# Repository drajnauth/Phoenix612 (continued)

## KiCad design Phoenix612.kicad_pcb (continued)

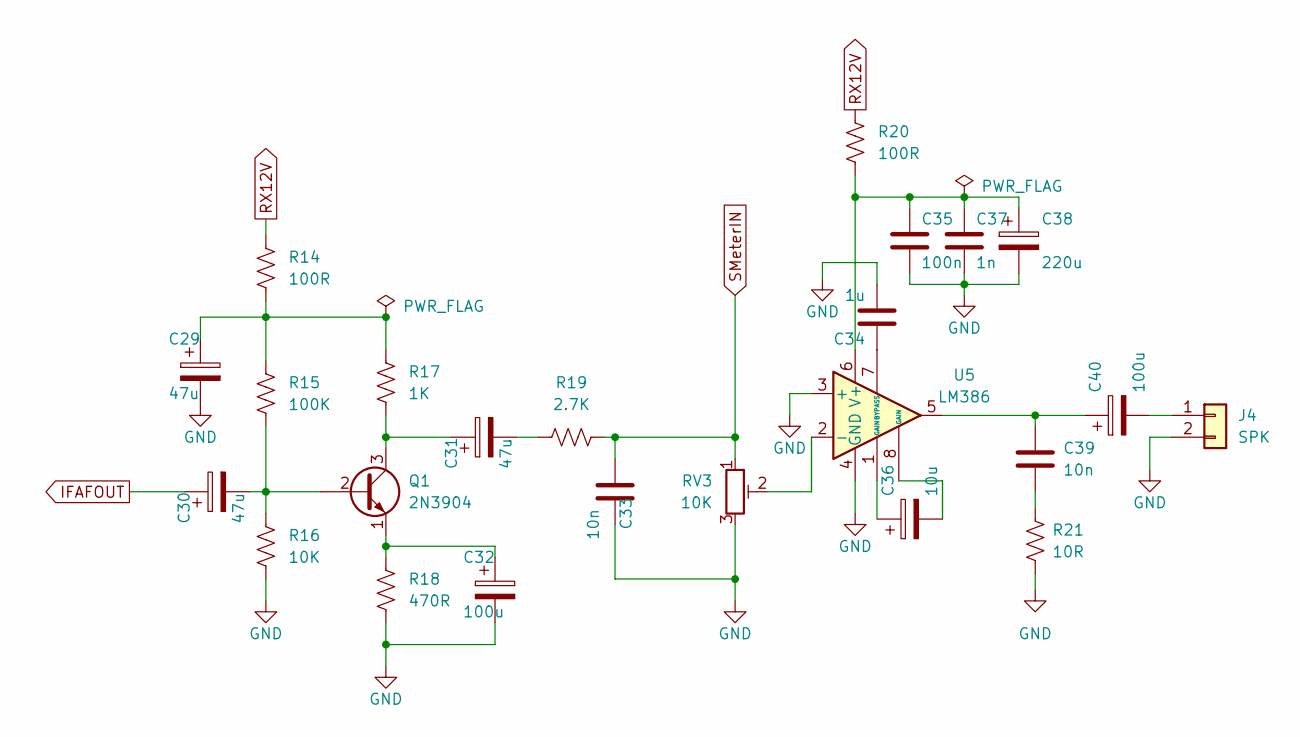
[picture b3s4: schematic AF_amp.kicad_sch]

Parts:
C29, C30, C31: 47u; CP_Radial_D8.0mm_P2.50mm
C32, C40: 100u; CP_Radial_D8.0mm_P2.50mm
C33, C39: 10n; C_Disc_D3.4mm_W2.1mm_P2.50mm
C34: 1u; C_Disc_D3.4mm_W2.1mm_P2.50mm
C35: 100n; C_Disc_D3.4mm_W2.1mm_P2.50mm
C36: 10u; CP_Radial_D8.0mm_P2.50mm
C37: 1n; C_Disc_D3.4mm_W2.1mm_P2.50mm
C38: 220u; CP_Radial_D8.0mm_P2.50mm
J4: SPK; PinHeader_1x02_P2.54mm_Vertical
Q1: 2N3904; TO-92_Inline
R14, R20: 100R; R_Axial_DIN0207_L6.3mm_D2.5mm_P10.16mm_Horizontal
R15: 100K; R_Axial_DIN0207_L6.3mm_D2.5mm_P10.16mm_Horizontal
R16: 10K; R_Axial_DIN0207_L6.3mm_D2.5mm_P10.16mm_Horizontal
R17: 1K; R_Axial_DIN0207_L6.3mm_D2.5mm_P10.16mm_Horizontal
R18: 470R; R_Axial_DIN0207_L6.3mm_D2.5mm_P10.16mm_Horizontal
R19: 2.7K; R_Axial_DIN0207_L6.3mm_D2.5mm_P10.16mm_Horizontal
R21: 10R; R_Axial_DIN0207_L6.3mm_D2.5mm_P10.16mm_Horizontal
RV3: 10K; Potentiometer_Bourns_3296W_Vertical
U5: LM386; DIP-8_W7.62mm_Socket

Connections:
GND: C29.2, C32.2, C33.2, C34.2, C35.2, C37.2, C38.2, J4.2, R16.2, R18.2, R21.1, RV3.3, U5.3 (+), U5.4 (GND); also elsewhere on the board
IFAFOUT: C30.1; also elsewhere on the board
unnamed: C29.1, R14.2, R15.1, R17.1
unnamed: C30.2, Q1.2 (B), R15.2, R16.1
unnamed: C31.1, Q1.3 (C), R17.2
unnamed: C31.2, R19.1
unnamed: C32.1, Q1.1 (E), R18.1
unnamed: C34.1, U5.7 (BYPASS)
unnamed: C35.1, C37.1, C38.1, R20.2, U5.6 (V+)
unnamed: C36.1, U5.1 (GAIN)
unnamed: C36.2, U5.8 (GAIN)
unnamed: C39.1, C40.1, U5.5
unnamed: C39.2, R21.2
unnamed: C40.2, J4.1
unnamed: RV3.2, U5.2 (-)
RX12V: R14.1, R20.1; also elsewhere on the board
SMeterIN: C33.1, R19.2, RV3.1; also elsewhere on the board

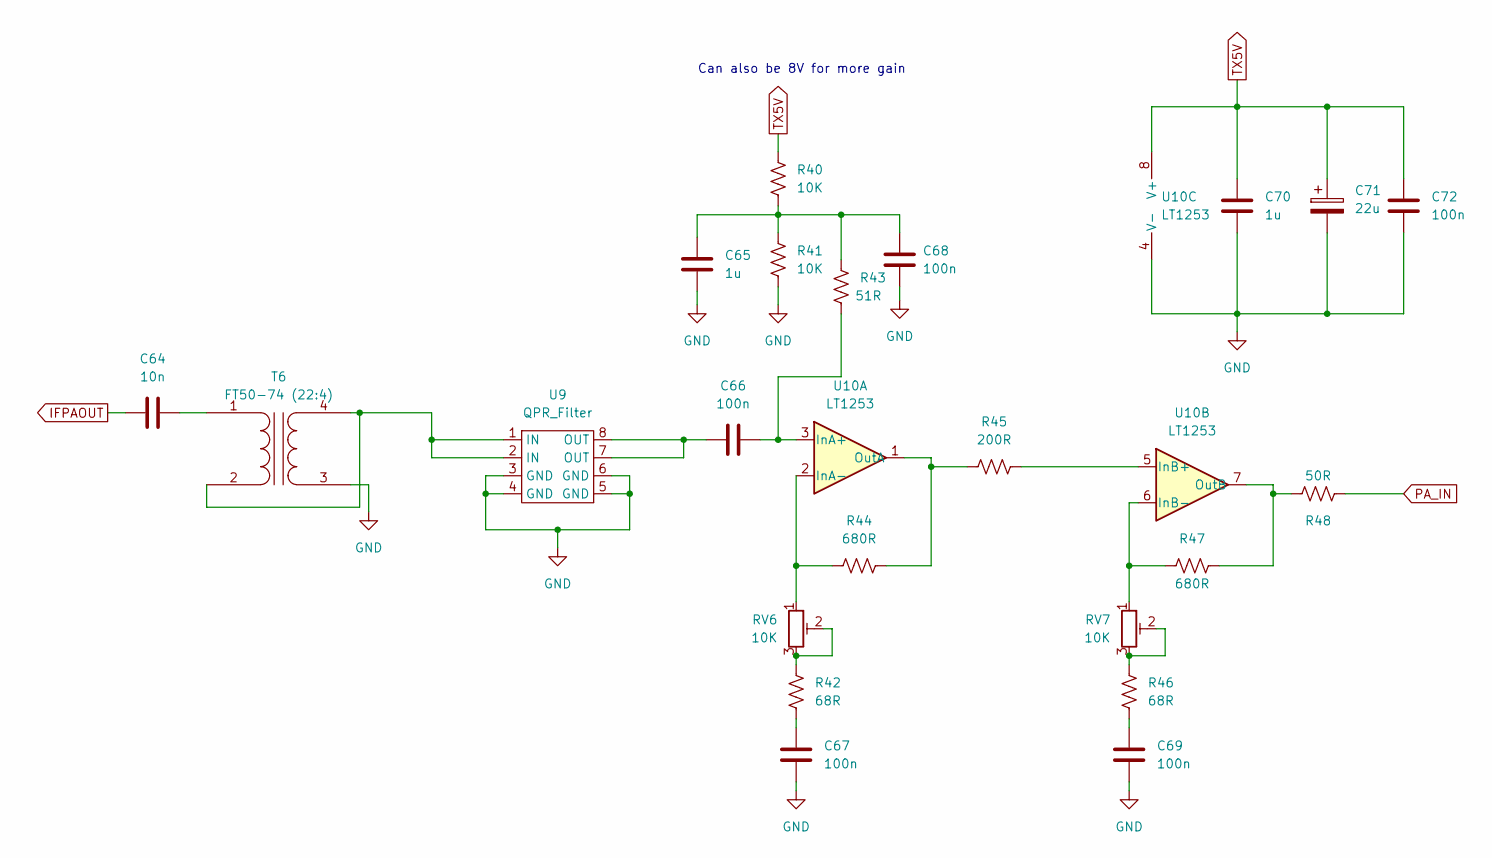
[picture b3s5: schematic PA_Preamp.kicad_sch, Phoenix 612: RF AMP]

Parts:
C64: 10n; C_Disc_D3.4mm_W2.1mm_P2.50mm
C65, C70: 1u; C_Disc_D3.4mm_W2.1mm_P2.50mm
C66, C67, C68, C69, C72: 100n; C_Disc_D3.4mm_W2.1mm_P2.50mm
C71: 22u; CP_Radial_D8.0mm_P2.50mm
R40, R41: 10K; R_Axial_DIN0207_L6.3mm_D2.5mm_P10.16mm_Horizontal
R42, R46: 68R; R_Axial_DIN0207_L6.3mm_D2.5mm_P10.16mm_Horizontal
R43: 51R; R_Axial_DIN0207_L6.3mm_D2.5mm_P10.16mm_Horizontal
R44, R47: 680R; R_Axial_DIN0207_L6.3mm_D2.5mm_P10.16mm_Horizontal
R45: 200R; R_Axial_DIN0207_L6.3mm_D2.5mm_P10.16mm_Horizontal
R48: 50R; R_Axial_DIN0207_L6.3mm_D2.5mm_P10.16mm_Horizontal
RV6, RV7: 10K; Potentiometer_Bourns_3296W_Vertical
T6: FT50-74 (22:4); Transformer_Toroid_Horizontal_D14.0mm_Amidon-T50
U9: QPR_Filter; QRPLabs_Filter_TH
U10: LT1253; DIP-8_W7.62mm

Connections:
GND: C65.2, C67.2, C68.2, C69.2, C70.2, C71.2, C72.2, R41.2, T6.3 (SA), U9.3 (GND), U9.4 (GND), U9.5 (GND), U9.6 (GND), U10.4 (V-); also elsewhere on the board
IFPAOUT: C64.1; also elsewhere on the board
unnamed: C64.2, T6.1 (AA)
unnamed: C65.1, C68.1, R40.2, R41.1, R43.2
unnamed: C66.1, U9.7 (OUT), U9.8 (OUT)
unnamed: C66.2, R43.1, U10.3 (InA+)
unnamed: C67.1, R42.2
unnamed: C69.1, R46.2
unnamed: R42.1, RV6.2, RV6.3
unnamed: R44.1, RV6.1, U10.2 (InA-)
unnamed: R44.2, R45.1, U10.1 (OutA)
unnamed: R45.2, U10.5 (InB+)
unnamed: R46.1, RV7.2, RV7.3
unnamed: R47.1, R48.1, U10.7 (OutB)
unnamed: R47.2, RV7.1, U10.6 (InB-)
unnamed: T6.2 (AB), T6.4 (SB), U9.1 (IN), U9.2 (IN)
PA_IN: R48.2; also elsewhere on the board
TX5V: C70.1, C71.1, C72.1, R40.1, U10.8 (V+); also elsewhere on the board

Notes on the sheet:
Can also be 8V for more gain

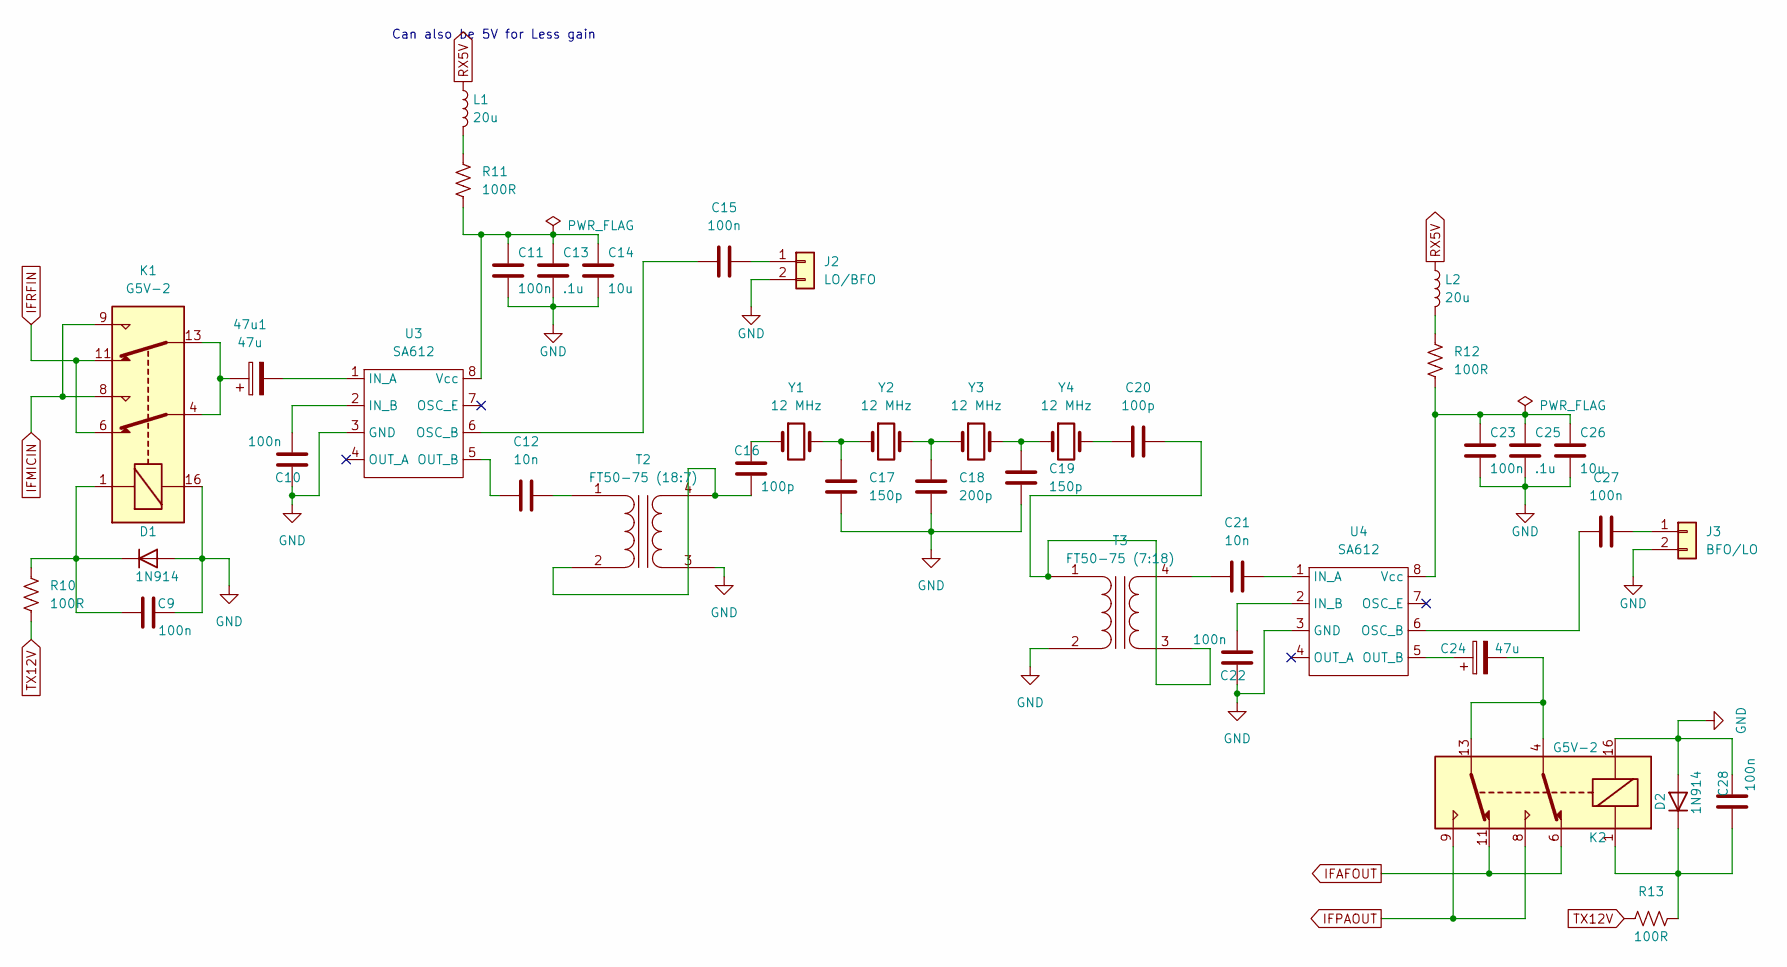
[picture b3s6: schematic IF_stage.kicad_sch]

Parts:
47u1: 47u; CP_Radial_D8.0mm_P2.50mm
C9, C10, C11, C15, C22, C23, C27, C28: 100n; C_Disc_D3.4mm_W2.1mm_P2.50mm
C12, C21: 10n; C_Disc_D3.4mm_W2.1mm_P2.50mm
C13, C25: .1u; C_Disc_D3.4mm_W2.1mm_P2.50mm
C14, C26: 10u; C_Disc_D3.4mm_W2.1mm_P2.50mm
C16, C20: 100p; C_Disc_D3.4mm_W2.1mm_P2.50mm
C17, C19: 150p; C_Disc_D3.4mm_W2.1mm_P2.50mm
C18: 200p; C_Disc_D3.4mm_W2.1mm_P2.50mm
C24: 47u; CP_Radial_D8.0mm_P2.50mm
D1, D2: 1N914; D_DO-35_SOD27_P7.62mm_Horizontal
J2: LO/BFO; PinHeader_1x02_P2.54mm_Vertical
J3: BFO/LO; PinHeader_1x02_P2.54mm_Vertical
K1, K2: G5V-2; Relay_DPDT_Omron_G5V-2
L1, L2: 20u; L_1206_3216Metric
R10, R11, R12, R13: 100R; R_Axial_DIN0207_L6.3mm_D2.5mm_P10.16mm_Horizontal
T2: FT50-75 (18:7); Transformer_Toroid_Horizontal_D14.0mm_Amidon-T50
T3: FT50-75 (7:18); Transformer_Toroid_Horizontal_D14.0mm_Amidon-T50
U3, U4: SA612; DIP-8_W7.62mm_Socket
Y1, Y2, Y3, Y4: 12 MHz; Crystal_HC49-4H_Vertical

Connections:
GND: C9.2, C10.2, C11.2, C13.2, C14.2, C17.2, C18.2, C19.2, C22.2, C23.2, C25.2, C26.2, C28.2, D1.2 (A), D2.2 (A), J2.2, J3.2, K1.16, K2.16, T2.3 (SA), T3.2 (AB), U3.3 (GND), U4.3 (GND); also elsewhere on the board
IFAFOUT: K2.6, K2.11; also elsewhere on the board
IFMICIN: K1.8, K1.9; also elsewhere on the board
IFPAOUT: K2.8, K2.9; also elsewhere on the board
IFRFIN: K1.6, K1.11; also elsewhere on the board
unnamed: 47u1.1, K1.4, K1.13
unnamed: 47u1.2, U3.1 (IN_A)
unnamed: C9.1, D1.1 (K), K1.1, R10.1
unnamed: C10.1, U3.2 (IN_B)
unnamed: C11.1, C13.1, C14.1, R11.2, U3.8 (Vcc)
unnamed: C12.1, U3.5 (OUT_B)
unnamed: C12.2, T2.1 (AA)
unnamed: C15.1, J2.1
unnamed: C15.2, U3.6 (OSC_B)
unnamed: C16.1, T2.2 (AB), T2.4 (SB)
unnamed: C16.2, Y1.1
unnamed: C17.1, Y1.2, Y2.1
unnamed: C18.1, Y2.2, Y3.1
unnamed: C19.1, Y3.2, Y4.1
unnamed: C20.1, Y4.2
unnamed: C20.2, T3.1 (AA), T3.3 (SA)
unnamed: C21.1, T3.4 (SB)
unnamed: C21.2, U4.1 (IN_A)
unnamed: C22.1, U4.2 (IN_B)
unnamed: C23.1, C25.1, C26.1, R12.2, U4.8 (Vcc)
unnamed: C24.1, U4.5 (OUT_B)
unnamed: C24.2, K2.4, K2.13
unnamed: C27.1, J3.1
unnamed: C27.2, U4.6 (OSC_B)
unnamed: C28.1, D2.1 (K), K2.1, R13.1
unnamed: L1.2, R11.1
unnamed: L2.2, R12.1
RX5V: L1.1, L2.1; also elsewhere on the board
TX12V: R10.2, R13.2; also elsewhere on the board

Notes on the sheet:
Can also be 5V for Less gain

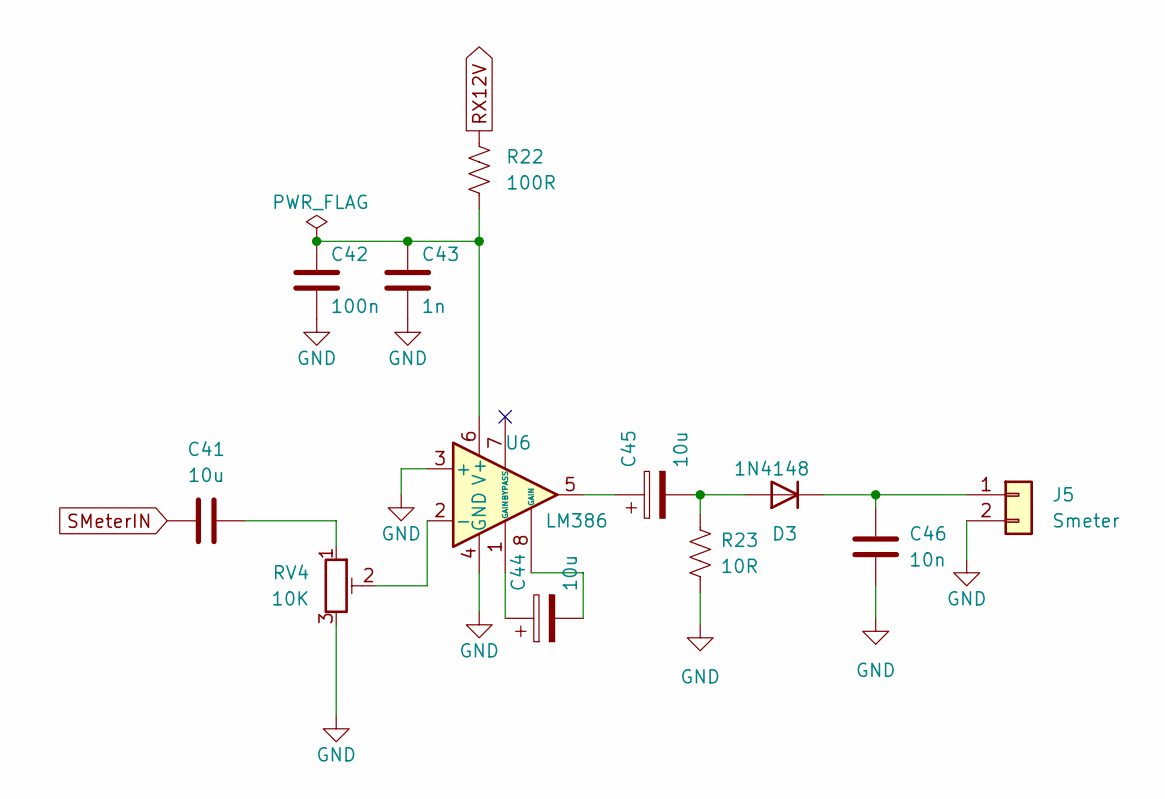
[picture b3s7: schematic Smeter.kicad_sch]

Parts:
C41: 10u; C_Disc_D3.4mm_W2.1mm_P2.50mm
C42: 100n; C_Disc_D3.4mm_W2.1mm_P2.50mm
C43: 1n; C_Disc_D3.4mm_W2.1mm_P2.50mm
C44, C45: 10u; CP_Radial_D8.0mm_P2.50mm
C46: 10n; C_Disc_D3.4mm_W2.1mm_P2.50mm
D3: 1N4148; D_DO-35_SOD27_P7.62mm_Horizontal
J5: Smeter; PinHeader_1x02_P2.54mm_Vertical
R22: 100R; R_Axial_DIN0207_L6.3mm_D2.5mm_P10.16mm_Horizontal
R23: 10R; R_Axial_DIN0207_L6.3mm_D2.5mm_P10.16mm_Horizontal
RV4: 10K; Potentiometer_Bourns_3296W_Vertical
U6: LM386; DIP-8_W7.62mm_Socket

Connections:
GND: C42.2, C43.2, C46.2, J5.2, R23.1, RV4.3, U6.3 (+), U6.4 (GND); also elsewhere on the board
unnamed: C41.2, RV4.1
unnamed: C42.1, C43.1, R22.2, U6.6 (V+)
unnamed: C44.1, U6.1 (GAIN)
unnamed: C44.2, U6.8 (GAIN)
unnamed: C45.1, U6.5
unnamed: C45.2, D3.2 (A), R23.2
unnamed: C46.1, D3.1 (K), J5.1
unnamed: RV4.2, U6.2 (-)
RX12V: R22.1; also elsewhere on the board
SMeterIN: C41.1; also elsewhere on the board

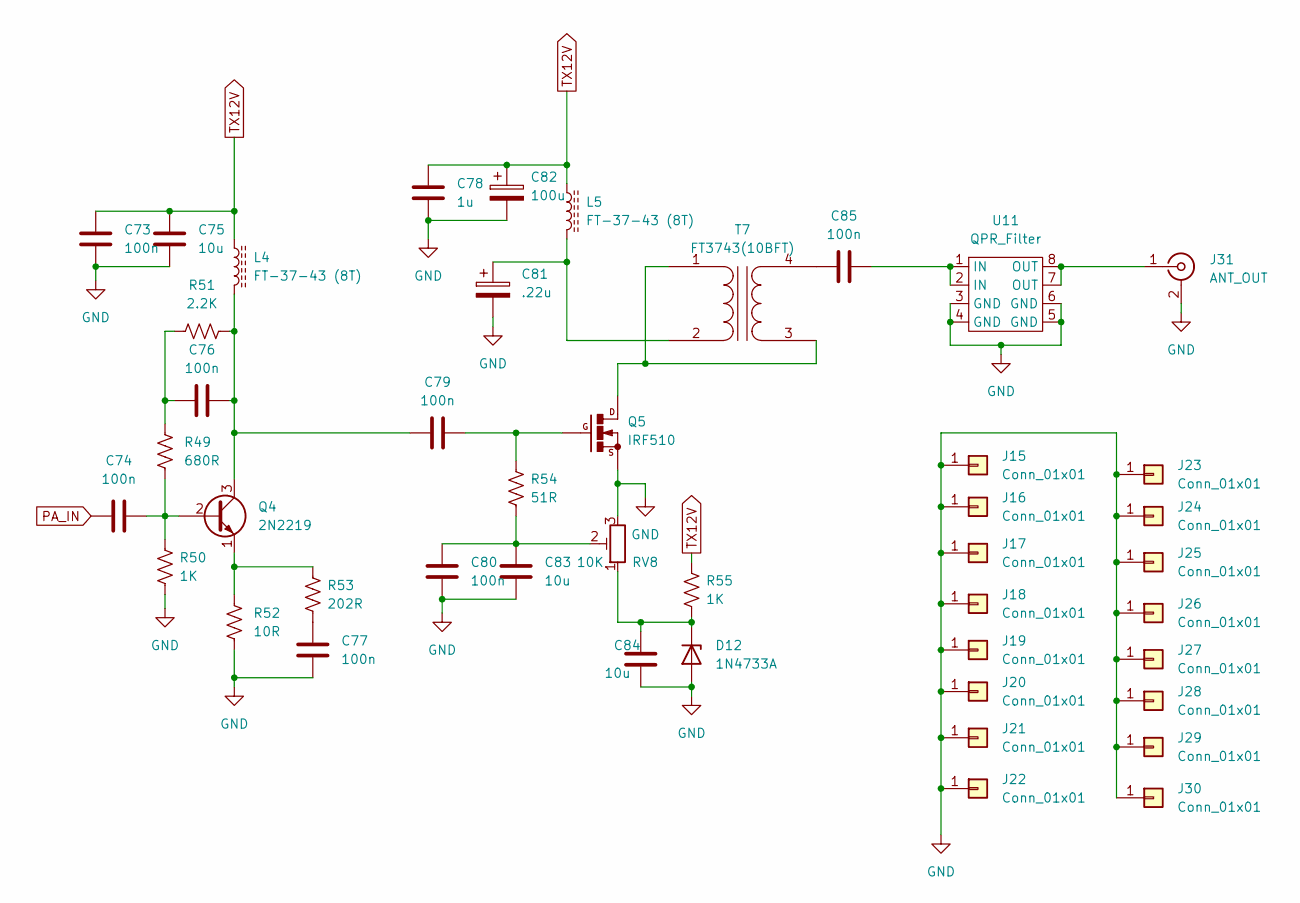
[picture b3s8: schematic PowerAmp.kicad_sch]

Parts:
C73, C74, C76, C77, C79, C80, C85: 100n; C_Disc_D3.4mm_W2.1mm_P2.50mm
C75, C83, C84: 10u; C_Disc_D3.4mm_W2.1mm_P2.50mm
C78: 1u; C_Disc_D3.4mm_W2.1mm_P2.50mm
C81: .22u; CP_Radial_D8.0mm_P2.50mm
C82: 100u; CP_Radial_D8.0mm_P2.50mm
D12: 1N4733A; D_DO-41_SOD81_P10.16mm_Horizontal
J15, J16, J17, J18, J19, J20, J21, J22, J23, J24, J25, J26, J27, J28, J29, J30: Conn_01x01; TestPoint_Pad_2.0x2.0mm
J31: ANT_OUT; SMA_Amphenol_901-144_Vertical
L4, L5: FT-37-43 (8T); L_Toroid_Horizontal_D9.5mm_P15.00mm_Diameter10-5mm_Amidon-T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
Q4: 2N2219; TO-39-3
Q5: IRF510; TO-220-3_Vertical
R49: 680R; R_Axial_DIN0207_L6.3mm_D2.5mm_P10.16mm_Horizontal
R50, R55: 1K; R_Axial_DIN0207_L6.3mm_D2.5mm_P10.16mm_Horizontal
R51: 2.2K; R_Axial_DIN0207_L6.3mm_D2.5mm_P10.16mm_Horizontal
R52: 10R; R_Axial_DIN0207_L6.3mm_D2.5mm_P10.16mm_Horizontal
R53: 202R; R_Axial_DIN0207_L6.3mm_D2.5mm_P10.16mm_Horizontal
R54: 51R; R_Axial_DIN0207_L6.3mm_D2.5mm_P10.16mm_Horizontal
RV8: 10K; Potentiometer_Bourns_3296W_Vertical
T7: FT3743(10BFT); Transformer_Toroid_Horizontal_D10.5mm_Amidon-T37
U11: QPR_Filter; QRPLabs_Filter_TH

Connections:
GND: C73.2, C75.2, C77.2, C78.2, C80.2, C81.2, C82.2, C83.2, C84.2, D12.2 (A), J15.1, J16.1, J17.1, J18.1, J19.1, J20.1, J21.1, J22.1, J23.1, J24.1, J25.1, J26.1, J27.1, J28.1, J29.1, J30.1, J31.2 (Ext), Q5.1, R50.1, R52.1, RV8.3, U11.3 (GND), U11.4 (GND), U11.5 (GND), U11.6 (GND); also elsewhere on the board
unnamed: C74.2, Q4.2 (B), R49.1, R50.2
unnamed: C76.1, R49.2, R51.1
unnamed: C76.2, C79.1, L4.2, Q4.3 (C), R51.2
unnamed: C77.1, R53.1
unnamed: C79.2, Q5.3, R54.2
unnamed: C80.1, C83.1, R54.1, RV8.2
unnamed: C81.1, L5.2, T7.2 (AB)
unnamed: C84.1, D12.1 (K), R55.2, RV8.1
unnamed: C85.1, T7.4 (SB)
unnamed: C85.2, U11.1 (IN), U11.2 (IN)
unnamed: J31.1 (In), U11.7 (OUT), U11.8 (OUT)
unnamed: Q4.1 (E), R52.2, R53.2
unnamed: Q5.2, T7.1 (AA), T7.3 (SA)
PA_IN: C74.1; also elsewhere on the board
TX12V: C73.1, C75.1, C78.1, C82.1, L4.1, L5.1, R55.1; also elsewhere on the board

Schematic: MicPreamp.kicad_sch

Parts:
C47: 100n; C_Disc_D3.4mm_W2.1mm_P2.50mm
C48, C53: 10n; C_Disc_D3.4mm_W2.1mm_P2.50mm
C49: 1n; C_Disc_D3.4mm_W2.1mm_P2.50mm
C50, C51, C52: 47u; CP_Radial_D8.0mm_P2.50mm
J6: MICIN; PinHeader_1x02_P2.54mm_Vertical
L3: 20u; L_1206_3216Metric
Q2: 2N3904; TO-92_Inline
R24: 100R; R_Axial_DIN0207_L6.3mm_D2.5mm_P10.16mm_Horizontal
R25, R26, R28: 10K; R_Axial_DIN0207_L6.3mm_D2.5mm_P10.16mm_Horizontal
R27: 220R; R_Axial_DIN0207_L6.3mm_D2.5mm_P10.16mm_Horizontal
R29: 10R; R_Axial_DIN0207_L6.3mm_D2.5mm_P10.16mm_Horizontal
RV5: 10K; Potentiometer_Bourns_3296W_Vertical

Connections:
GND: C47.2, C48.2, C49.2, C50.2, J6.1, Q2.1 (E), R26.2, R29.1, RV5.3; also elsewhere on the board
IFMICIN: C53.1, RV5.2; also elsewhere on the board
unnamed: C47.1, C49.1, C50.1, R24.2, R25.1, R28.1
unnamed: C48.1, J6.2, L3.1
unnamed: C51.1, L3.2, R25.2, R26.1
unnamed: C51.2, Q2.2 (B), R27.1
unnamed: C52.1, Q2.3 (C), R27.2, R28.2
unnamed: C52.2, RV5.1
unnamed: C53.2, R29.2
TX12V: R24.1; also elsewhere on the board

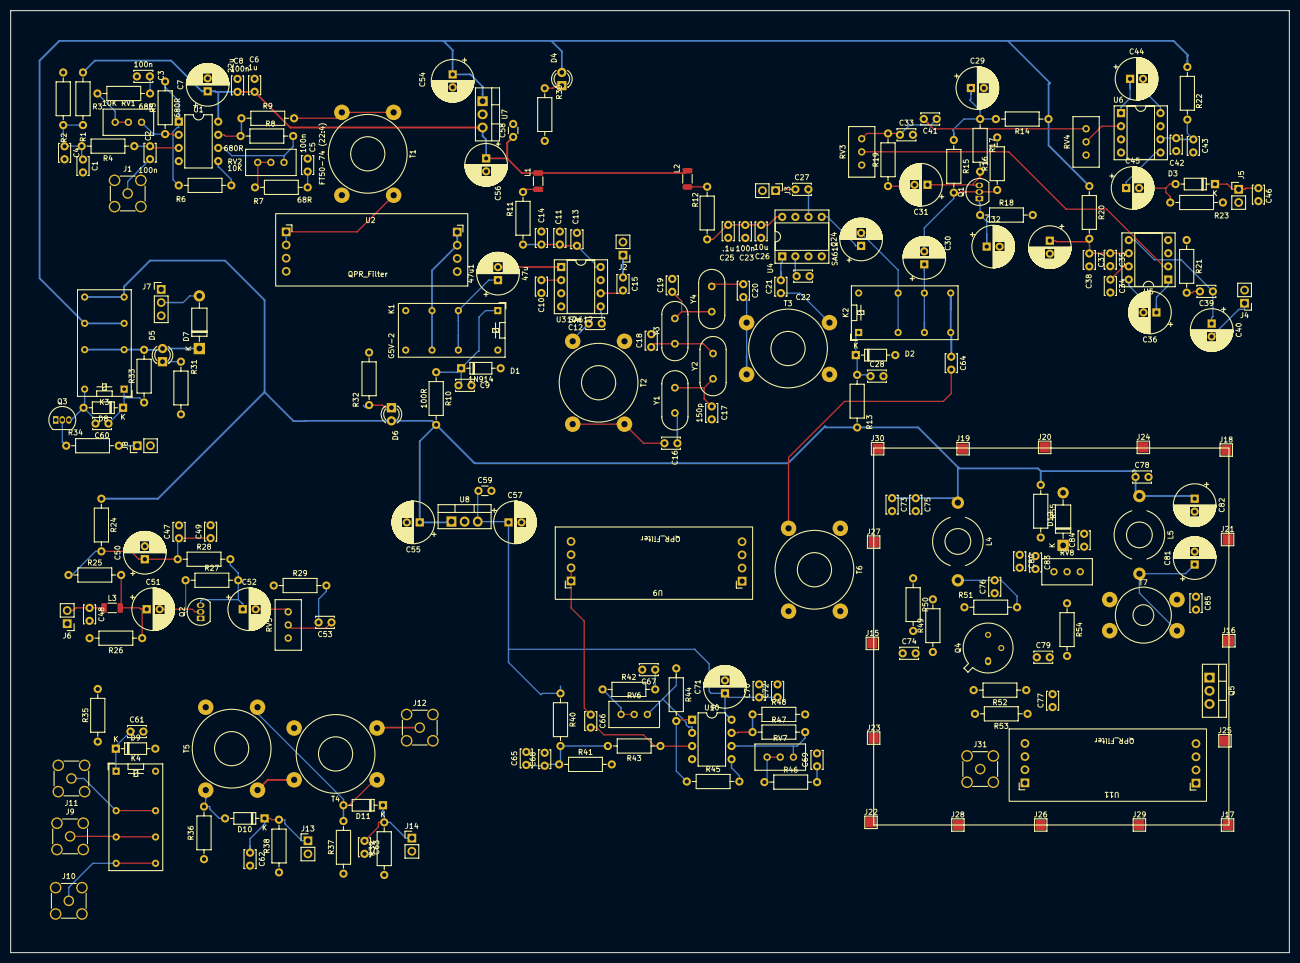
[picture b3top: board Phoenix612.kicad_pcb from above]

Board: 2 copper layers, 246.9 x 181.9 mm, 228 parts (0 on the bottom side), 126 nets.

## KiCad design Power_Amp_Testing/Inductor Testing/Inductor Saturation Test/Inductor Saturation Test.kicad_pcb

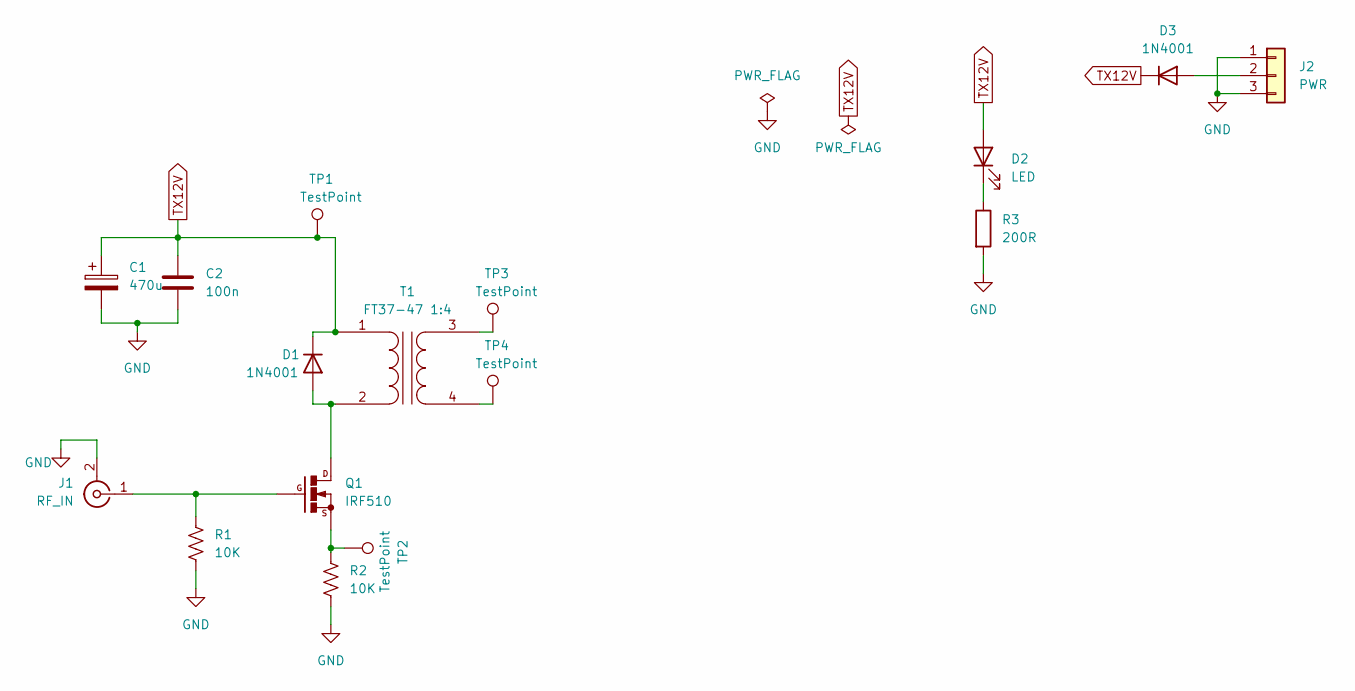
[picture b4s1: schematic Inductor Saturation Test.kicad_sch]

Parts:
C1: 470u; CP_Radial_D8.0mm_P2.50mm
C2: 100n; C_Disc_D5.0mm_W2.5mm_P5.00mm
D1, D3: 1N4001; D_DO-41_SOD81_P10.16mm_Horizontal
D2: LED; LED_D3.0mm
J1: RF_IN; SMA_Amphenol_901-144_Vertical
J2: PWR; PinHeader_1x03_P2.54mm_Vertical
Q1: IRF510; TO220
R1, R2: 10K; R_Axial_DIN0204_L3.6mm_D1.6mm_P5.08mm_Horizontal
R3: 200R; R_Axial_DIN0204_L3.6mm_D1.6mm_P5.08mm_Horizontal
T1: FT37-47 1:4; Transformer_Toroid_Horizontal_D10.5mm_Amidon-T37
TP1, TP2, TP3, TP4: TestPoint; PinHeader_1x01_P1.00mm_Vertical

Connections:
GND: C1.2, C2.2, J1.2 (Ext), J2.1, J2.3, R1.1, R2.1, R3.2
unnamed: D1.2 (A), Q1.2, T1.2 (AB)
unnamed: D2.1 (K), R3.1
unnamed: D3.2 (A), J2.2
unnamed: J1.1 (In), Q1.3, R1.2
unnamed: Q1.1, R2.2, TP2.1
unnamed: T1.3 (SB), TP3.1
unnamed: T1.4 (SA), TP4.1
TX12V: C1.1, C2.1, D1.1 (K), D2.2 (A), D3.1 (K), T1.1 (AA), TP1.1

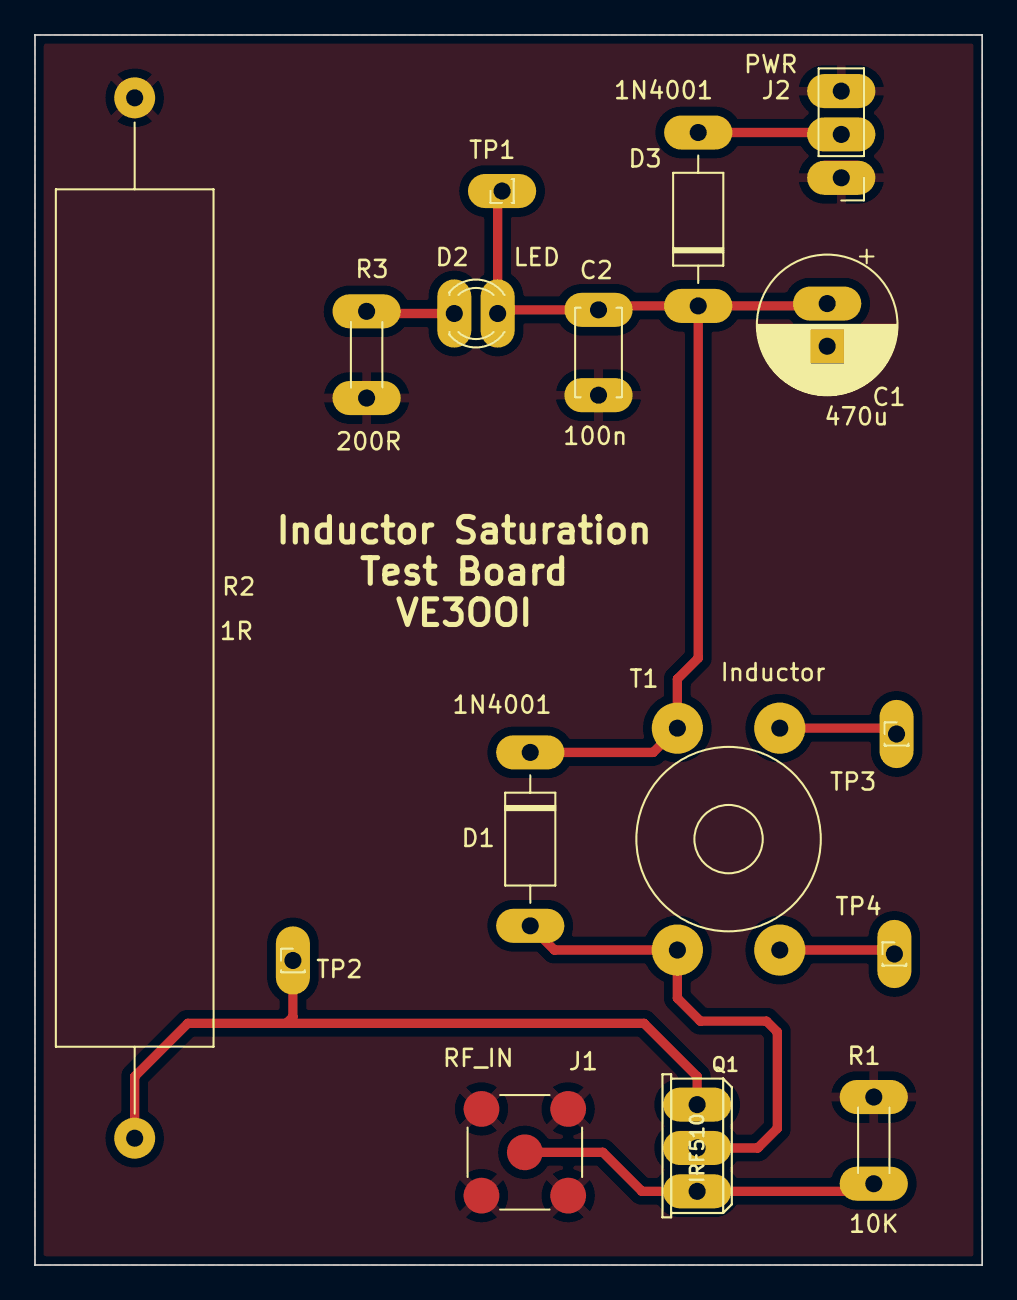
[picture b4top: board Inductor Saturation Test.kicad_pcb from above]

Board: 2 copper layers, 55.5 x 72.1 mm, 16 parts (0 on the bottom side), 9 nets.

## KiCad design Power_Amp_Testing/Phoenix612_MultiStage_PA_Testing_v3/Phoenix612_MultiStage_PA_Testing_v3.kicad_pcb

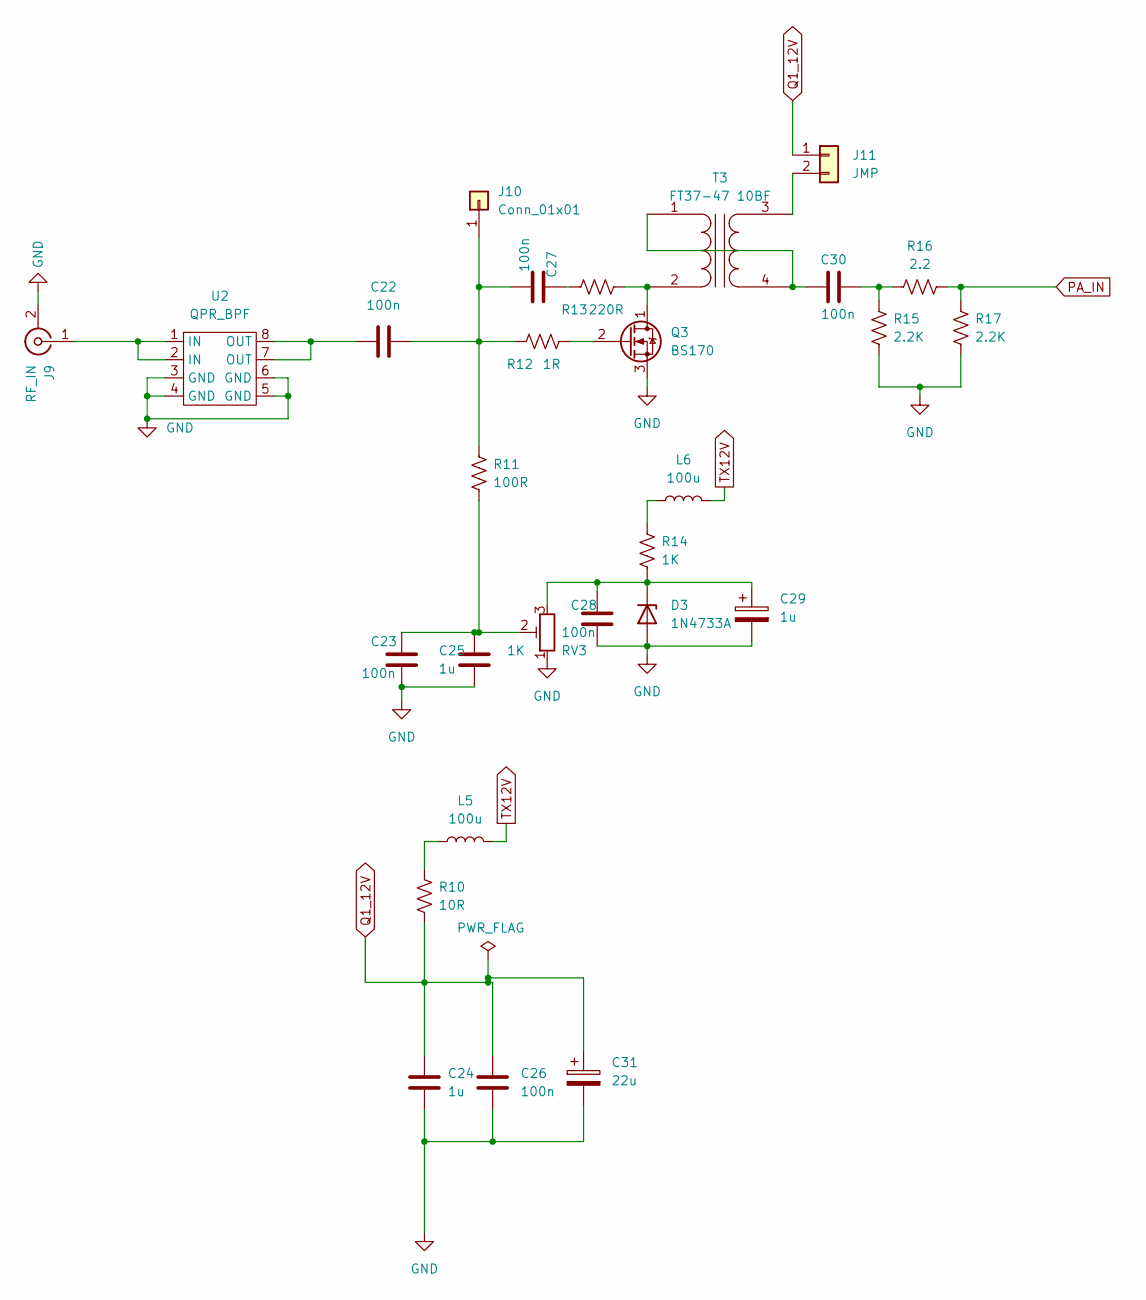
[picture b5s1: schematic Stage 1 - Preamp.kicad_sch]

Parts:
C22, C23, C26, C27, C28, C30: 100n; C_1206_3216Metric
C24, C25: 1u; C_1206_3216Metric
C29: 1u; CP_Radial_D8.0mm_P2.50mm
C31: 22u; CP_Radial_D5.0mm_P2.50mm
D3: 1N4733A; D_DO-41_SOD81_P10.16mm_Horizontal
J9: RF_IN; SMA_Amphenol_901-144_Vertical
J10: Conn_01x01; PinHeader_1x01_P1.00mm_Vertical
J11: JMP; PinHeader_1x02_P2.54mm_Vertical
L5, L6: 100u; L_1206_3216Metric_Pad1.42x1.75mm_HandSolder
Q3: BS170; TO-92_Inline_Wide
R10: 10R; R_1206_3216Metric
R11: 100R; R_1206_3216Metric
R12: 1R; R_1206_3216Metric
R13: 220R; R_1206_3216Metric
R14: 1K; R_1206_3216Metric
R15, R17: 2.2K; R_1206_3216Metric
R16: 2.2; R_1206_3216Metric
RV3: 1K; Potentiometer_Bourns_3296W_Vertical
T3: FT37-47 10BF; Transformer_Toroid_Horizontal_D10.5mm_Amidon-T37
U2: QPR_BPF; QRPLabs_Filter_TH

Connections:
GND: C23.2, C24.2, C25.2, C26.2, C28.2, C29.2, C31.2, D3.2 (A), J9.2 (Ext), Q3.3 (S), R15.1, R17.1, RV3.1, U2.3 (GND), U2.4 (GND), U2.5 (GND), U2.6 (GND); also elsewhere on the board
unnamed: C22.1, C27.2, J10.1, R11.2, R12.2
unnamed: C22.2, U2.7 (OUT), U2.8 (OUT)
unnamed: C23.1, C25.1, R11.1, RV3.2
unnamed: C27.1, R13.2
unnamed: C28.1, C29.1, D3.1 (K), R14.2, RV3.3
unnamed: C30.1, R15.2, R16.1
unnamed: C30.2, T3.1 (AA), T3.4 (SA)
unnamed: J9.1 (In), U2.1 (IN), U2.2 (IN)
unnamed: J11.2, T3.3 (SB)
unnamed: L5.1, R10.1
unnamed: L6.1, R14.1
unnamed: Q3.1 (D), R13.1, T3.2 (AB)
unnamed: Q3.2 (G), R12.1
PA_IN: R16.2, R17.2; also elsewhere on the board
Q1_12V: C24.1, C26.1, C31.1, J11.1, R10.2
TX12V: L5.2, L6.2; also elsewhere on the board

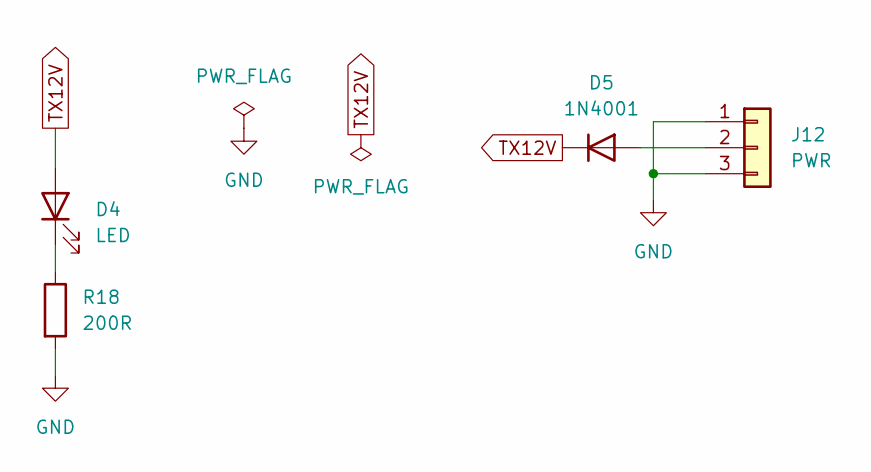
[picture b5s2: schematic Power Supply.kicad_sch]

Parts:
D4: LED; LED_D3.0mm
D5: 1N4001; D_DO-41_SOD81_P10.16mm_Horizontal
J12: PWR; PinHeader_1x03_P2.54mm_Vertical
R18: 200R; R_1206_3216Metric

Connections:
GND: J12.1, J12.3, R18.2; also elsewhere on the board
unnamed: D4.1 (K), R18.1
unnamed: D5.2 (A), J12.2
TX12V: D4.2 (A), D5.1 (K); also elsewhere on the board

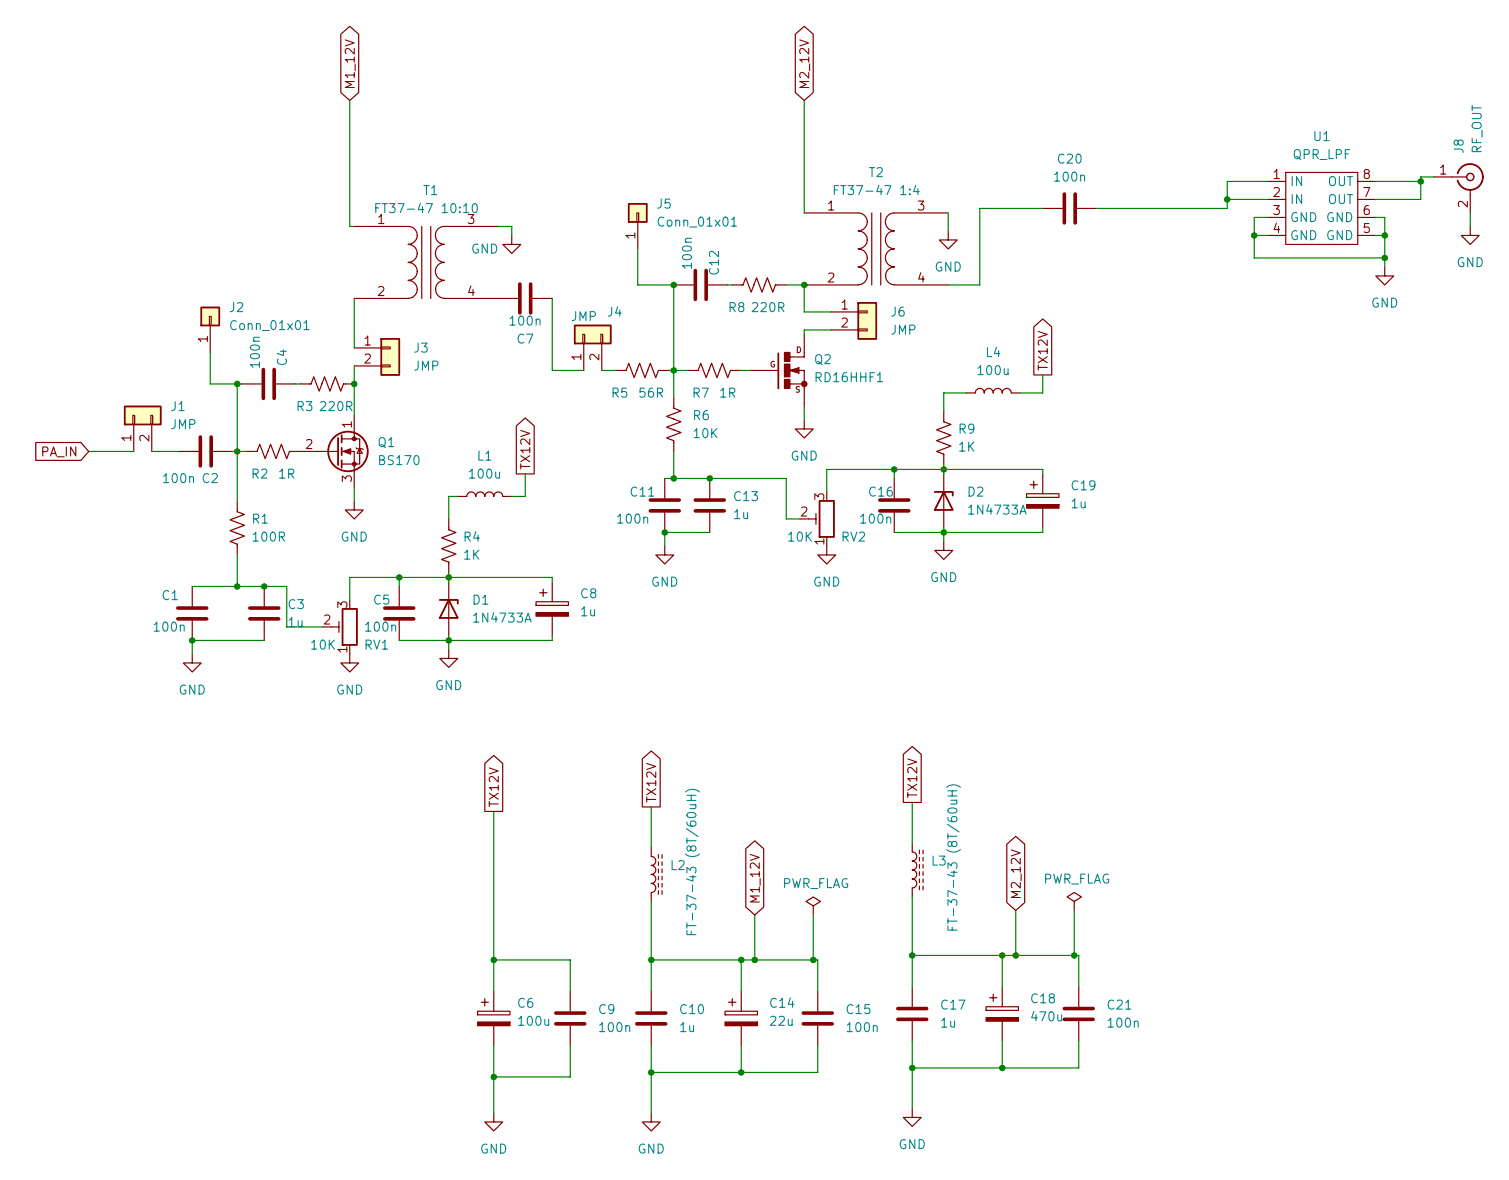
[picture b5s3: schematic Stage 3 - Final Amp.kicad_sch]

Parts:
C1, C2, C4, C5, C7, C9, C11, C12, C15, C16, C20, C21: 100n; C_1206_3216Metric
C3, C10, C13, C17: 1u; C_1206_3216Metric
C6: 100u; CP_Radial_D8.0mm_P2.50mm
C8, C19: 1u; CP_Radial_D8.0mm_P2.50mm
C14: 22u; CP_Radial_D8.0mm_P2.50mm
C18: 470u; CP_Radial_D8.0mm_P2.50mm
D1, D2: 1N4733A; D_DO-41_SOD81_P10.16mm_Horizontal
J1, J3, J4, J6: JMP; PinHeader_1x02_P2.54mm_Vertical
J2, J5: Conn_01x01; PinHeader_1x01_P1.00mm_Vertical
J8: RF_OUT; SMA_Amphenol_901-144_Vertical
L1, L4: 100u; L_1206_3216Metric_Pad1.42x1.75mm_HandSolder
L2, L3: FT-37-43 (8T/60uH); L_Toroid_Horizontal_D9.5mm_P15.00mm_Diameter10-5mm_Amidon-T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
Q1: BS170; TO-92_Inline_Wide
Q2: RD16HHF1; TO-220-3
R1: 100R; R_1206_3216Metric
R2, R7: 1R; R_1206_3216Metric
R3, R8: 220R; R_1206_3216Metric
R4, R9: 1K; R_1206_3216Metric
R5: 56R; R_1206_3216Metric
R6: 10K; R_1206_3216Metric
RV1, RV2: 10K; Potentiometer_Bourns_3296W_Vertical
T1: FT37-47 10:10; Transformer_Toroid_Horizontal_D10.5mm_Amidon-T37
T2: FT37-47 1:4; Transformer_Toroid_Horizontal_D10.5mm_Amidon-T37
U1: QPR_LPF; QRPLabs_Filter_TH

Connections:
GND: C1.2, C3.2, C5.2, C6.2, C8.2, C9.2, C10.2, C11.2, C13.2, C14.2, C15.2, C16.2, C17.2, C18.2, C19.2, C21.2, D1.2 (A), D2.2 (A), J8.2 (Ext), Q1.3 (S), Q2.2, RV1.1, RV2.1, T1.3 (SB), T2.3 (SB), U1.3 (GND), U1.4 (GND), U1.5 (GND), U1.6 (GND); also elsewhere on the board
M1_12V: C10.1, C14.1, C15.1, L2.2, T1.1 (AA)
M2_12V: C17.1, C18.1, C21.1, L3.2, T2.1 (AA)
unnamed: C1.1, C3.1, R1.1, RV1.2
unnamed: C2.1, J1.2
unnamed: C2.2, C4.2, J2.1, R1.2, R2.2
unnamed: C4.1, R3.2
unnamed: C5.1, C8.1, D1.1 (K), R4.2, RV1.3
unnamed: C7.1, T1.4 (SA)
unnamed: C7.2, J4.1
unnamed: C11.1, C13.1, R6.1, RV2.2
unnamed: C12.1, R8.2
unnamed: C12.2, J5.1, R5.1, R6.2, R7.2
unnamed: C16.1, C19.1, D2.1 (K), R9.2, RV2.3
unnamed: C20.1, T2.4 (SA)
unnamed: C20.2, U1.1 (IN), U1.2 (IN)
unnamed: J3.1, T1.2 (AB)
unnamed: J3.2, Q1.1 (D), R3.1
unnamed: J4.2, R5.2
unnamed: J6.1, R8.1, T2.2 (AB)
unnamed: J6.2, Q2.3
unnamed: J8.1 (In), U1.7 (OUT), U1.8 (OUT)
unnamed: L1.1, R4.1
unnamed: L4.1, R9.1
unnamed: Q1.2 (G), R2.1
unnamed: Q2.1, R7.1
PA_IN: J1.1; also elsewhere on the board
TX12V: C6.1, C9.1, L1.2, L2.1, L3.1, L4.2; also elsewhere on the board
